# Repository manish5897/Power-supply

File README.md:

# Power supply
Power supply Schematic and Layout

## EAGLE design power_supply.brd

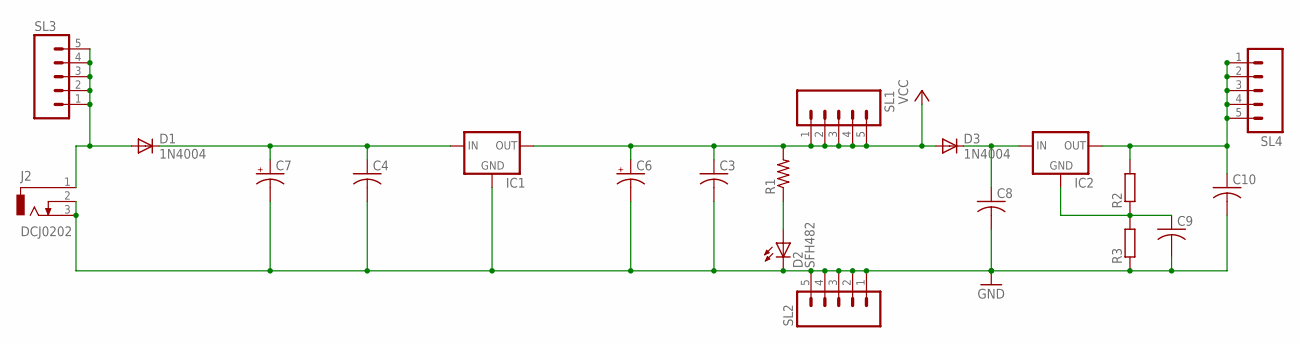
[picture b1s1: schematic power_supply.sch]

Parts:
C3, C4, C8, C9, C10: C-US025-025X050; C025-025X050
C6, C7: CPOL-USE3.5-10; E3,5-10
D1, D3: 1N4004; DO41-10
D2: SFH482
IC1, IC2: 78MXXS
J2: DCJ0202
R1: R-US_0204/7; 0204/7
R2, R3: R-EU_0204/7; 0204/7
SL1, SL2, SL3, SL4: M05; 05P

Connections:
GND: C3.2, C4.2, C6.-, C7.-, C8.2, C9.2, C10.2, D2.K (C), IC1.GND, J2.2, J2.3, R3.1, SL2.1, SL2.2, SL2.3, SL2.4, SL2.5
unnamed: C4.1, C7.+, D1.C, IC1.IN
unnamed: D2.A, R1.1
unnamed: D1.A, J2.1, SL3.1, SL3.2, SL3.3, SL3.4, SL3.5
unnamed: C8.1, D3.C, IC2.IN
unnamed: C10.1, IC2.OUT, R2.2, SL4.1, SL4.2, SL4.3, SL4.4, SL4.5
unnamed: C9.1, IC2.GND, R2.1, R3.2
VCC: C3.1, C6.+, D3.A, IC1.OUT, R1.2, SL1.1, SL1.2, SL1.3, SL1.4, SL1.5

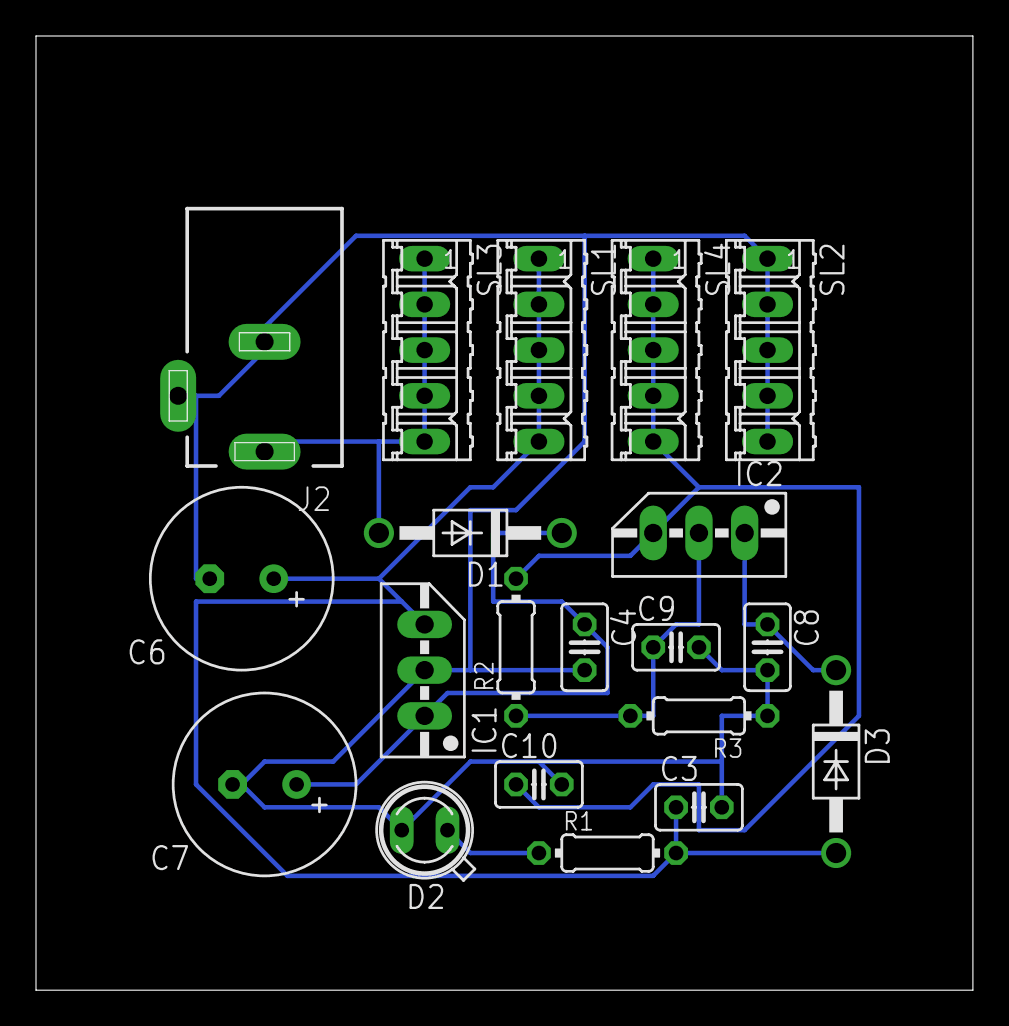
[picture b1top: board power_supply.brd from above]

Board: 2 copper layers, 52.0 x 53.0 mm, 20 parts (0 on the bottom side), 8 nets.

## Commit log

2018-08-12 power supply .sch and .brd file
2018-08-12 Power supply Schematic and Layout
